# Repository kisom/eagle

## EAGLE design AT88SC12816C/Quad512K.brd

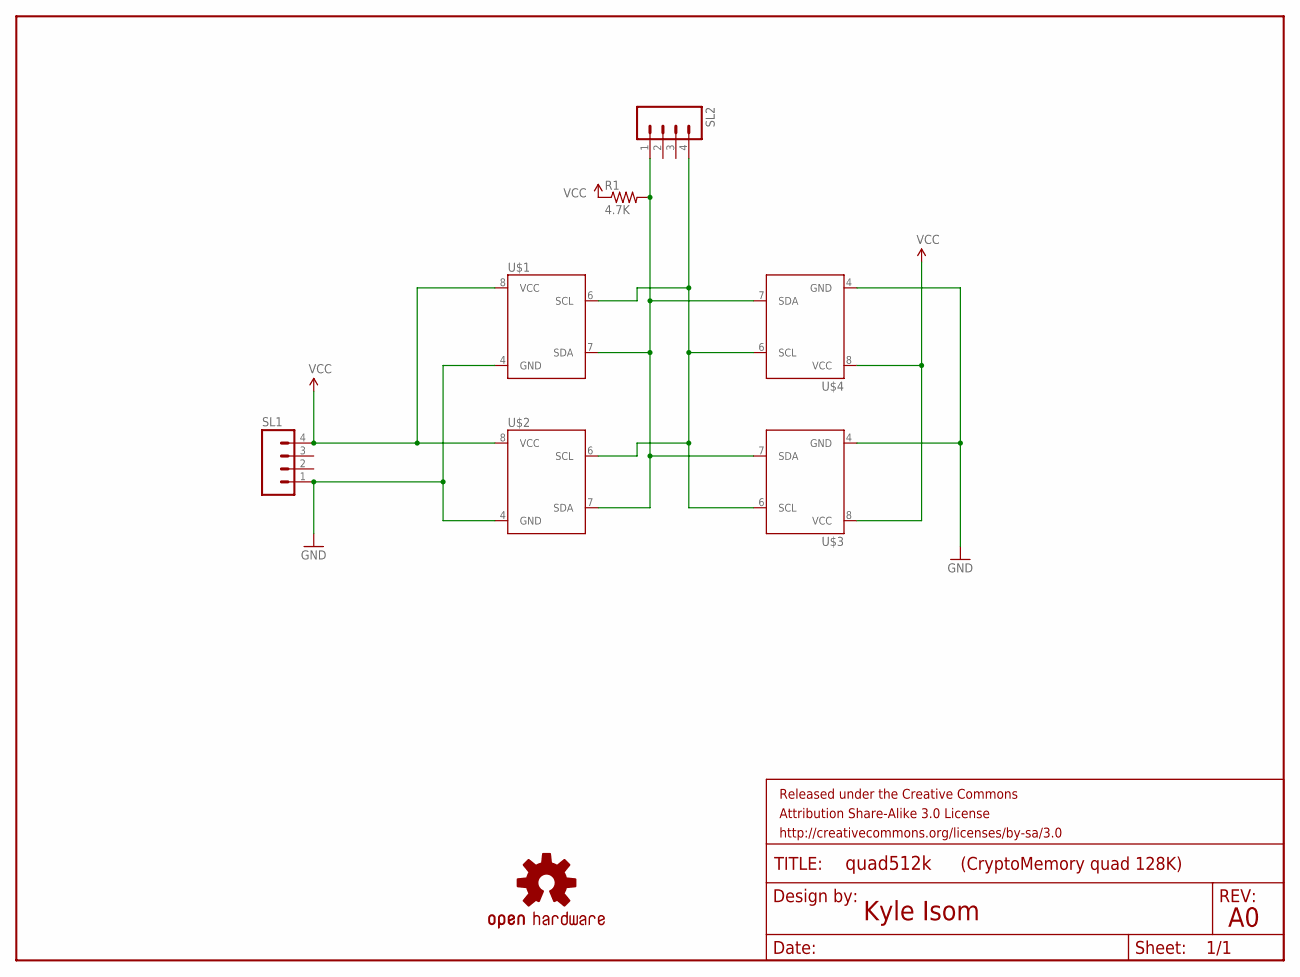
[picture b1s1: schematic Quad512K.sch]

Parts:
FRAME1: FRAME-LETTER; CREATIVE_COMMONS
LOGO1: OSHW-LOGOS; OSHW-LOGO-S
R1: 4.7K; AXIAL-0.4
SL1, SL2: M04LOCK; 1X04_LOCK
U$1, U$2, U$3, U$4: AT88SCAT88SC-PDIP; DIL08

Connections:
GND: SL1.1, U$1.4 (GND), U$2.4 (GND), U$3.4 (GND), U$4.4 (GND)
unnamed: SL2.4, U$1.6 (SCL), U$2.6 (SCL), U$3.6 (SCL), U$4.6 (SCL)
unnamed: R1.P$2 (2), SL2.1, U$1.7 (SDA), U$2.7 (SDA), U$3.7 (SDA), U$4.7 (SDA)
VCC: R1.P$1 (1), SL1.4, U$1.8 (VCC), U$2.8 (VCC), U$3.8 (VCC), U$4.8 (VCC)

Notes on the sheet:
(CryptoMemory quad 128K)
Kyle Isom

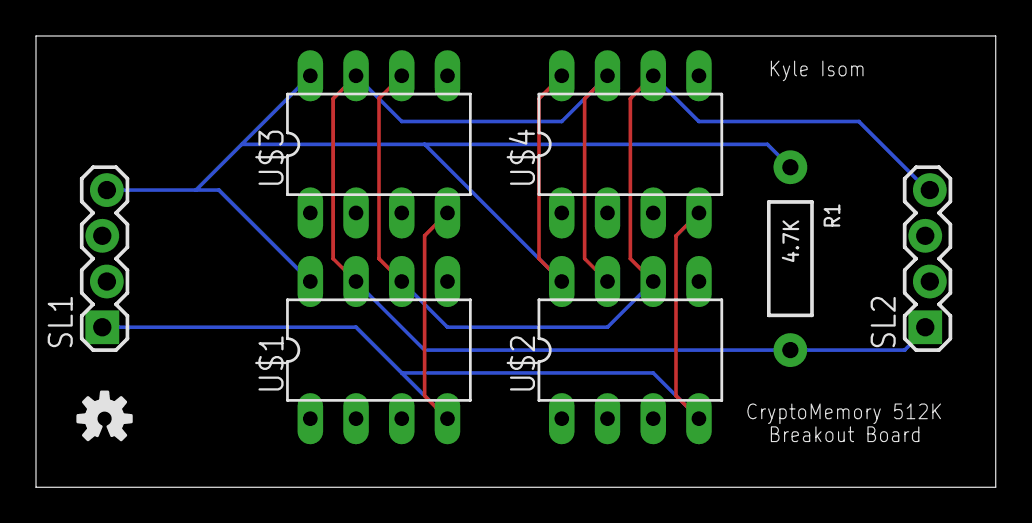
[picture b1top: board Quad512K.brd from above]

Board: 2 copper layers, 53.3 x 25.1 mm, 9 parts (0 on the bottom side), 4 nets.

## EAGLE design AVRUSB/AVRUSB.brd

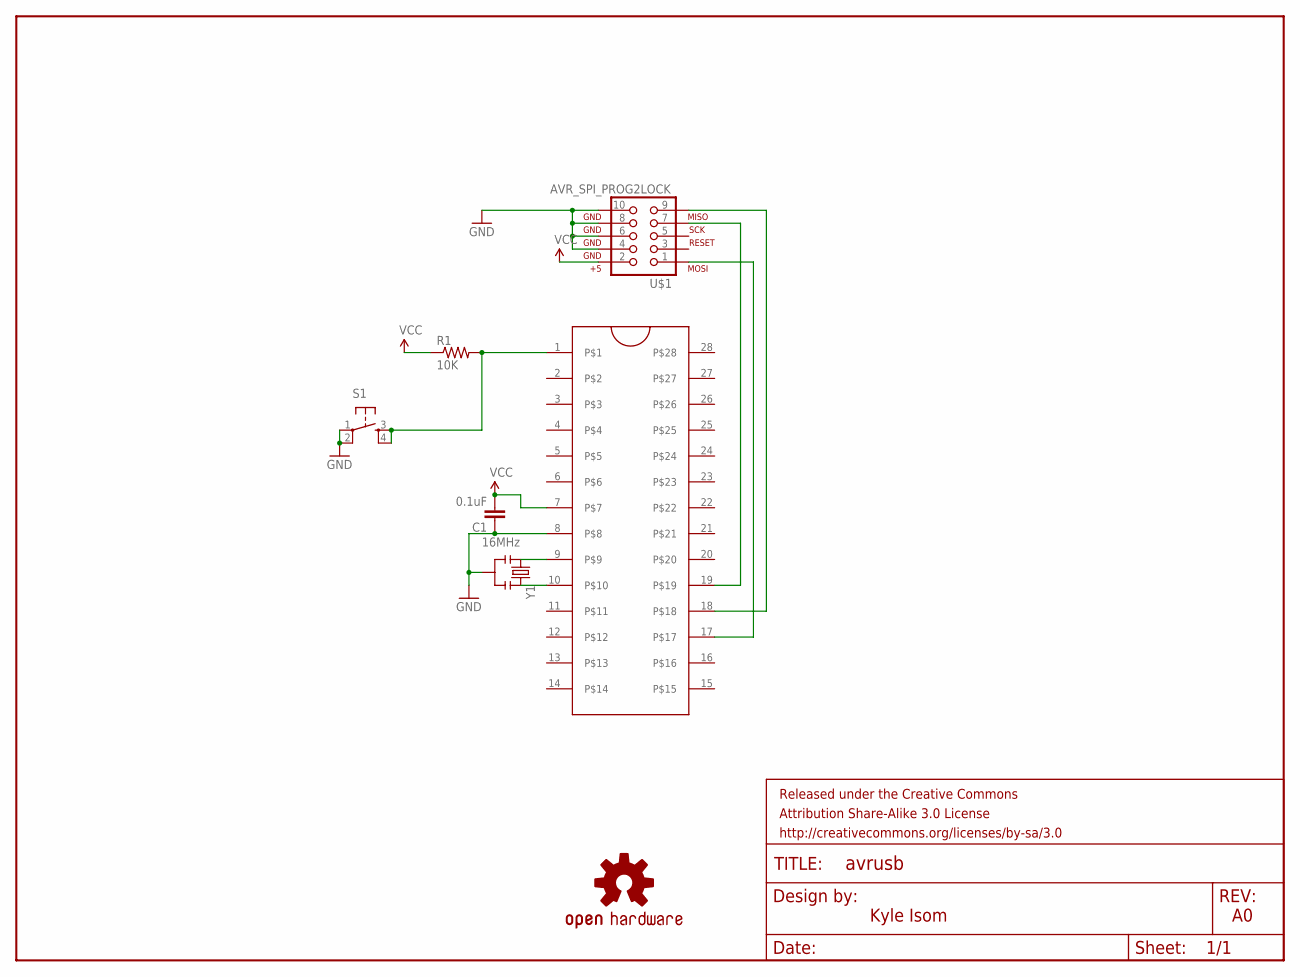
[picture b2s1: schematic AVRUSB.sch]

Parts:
C1: 0.1uF; CAP-PTH-SMALL
FRAME1: FRAME-LETTER; CREATIVE_COMMONS
LOGO1: OSHW-LOGOM; OSHW-LOGO-M
R1: 10K; AXIAL-0.4
S1: TAC_SWITCHPTH; TACTILE-PTH
U$1: AVR_SPI_PROG2LOCK; 2X5-SHROUDED_LOCK
U$2: ZIFSOCKET-28-3ZIFFSOCKET-28-3; DIL28-3-ZIF_SOCKET
Y1: 16MHz; RESONATOR-PTH

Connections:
GND: C1.1, S1.1, S1.2, U$1.4, U$1.6, U$1.8, U$1.10, U$2.8, Y1.2
unnamed: U$2.9, Y1.1
unnamed: U$2.10, Y1.3
unnamed: U$1.9, U$2.18
unnamed: U$1.1, U$2.17
unnamed: U$1.7, U$2.19
unnamed: R1.P$2 (2), S1.3, S1.4, U$2.1
VCC: C1.2, R1.P$1 (1), U$1.2, U$2.7

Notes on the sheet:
Kyle Isom

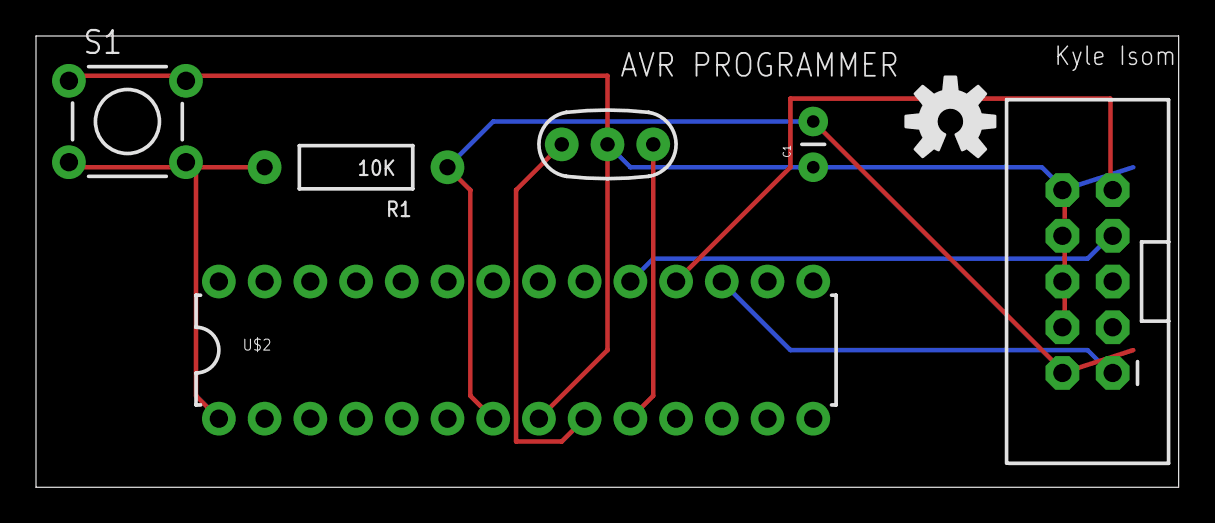
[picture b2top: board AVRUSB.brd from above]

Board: 2 copper layers, 63.5 x 25.1 mm, 9 parts (0 on the bottom side), 8 nets.

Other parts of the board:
U$3: OSHW-LOGO-M

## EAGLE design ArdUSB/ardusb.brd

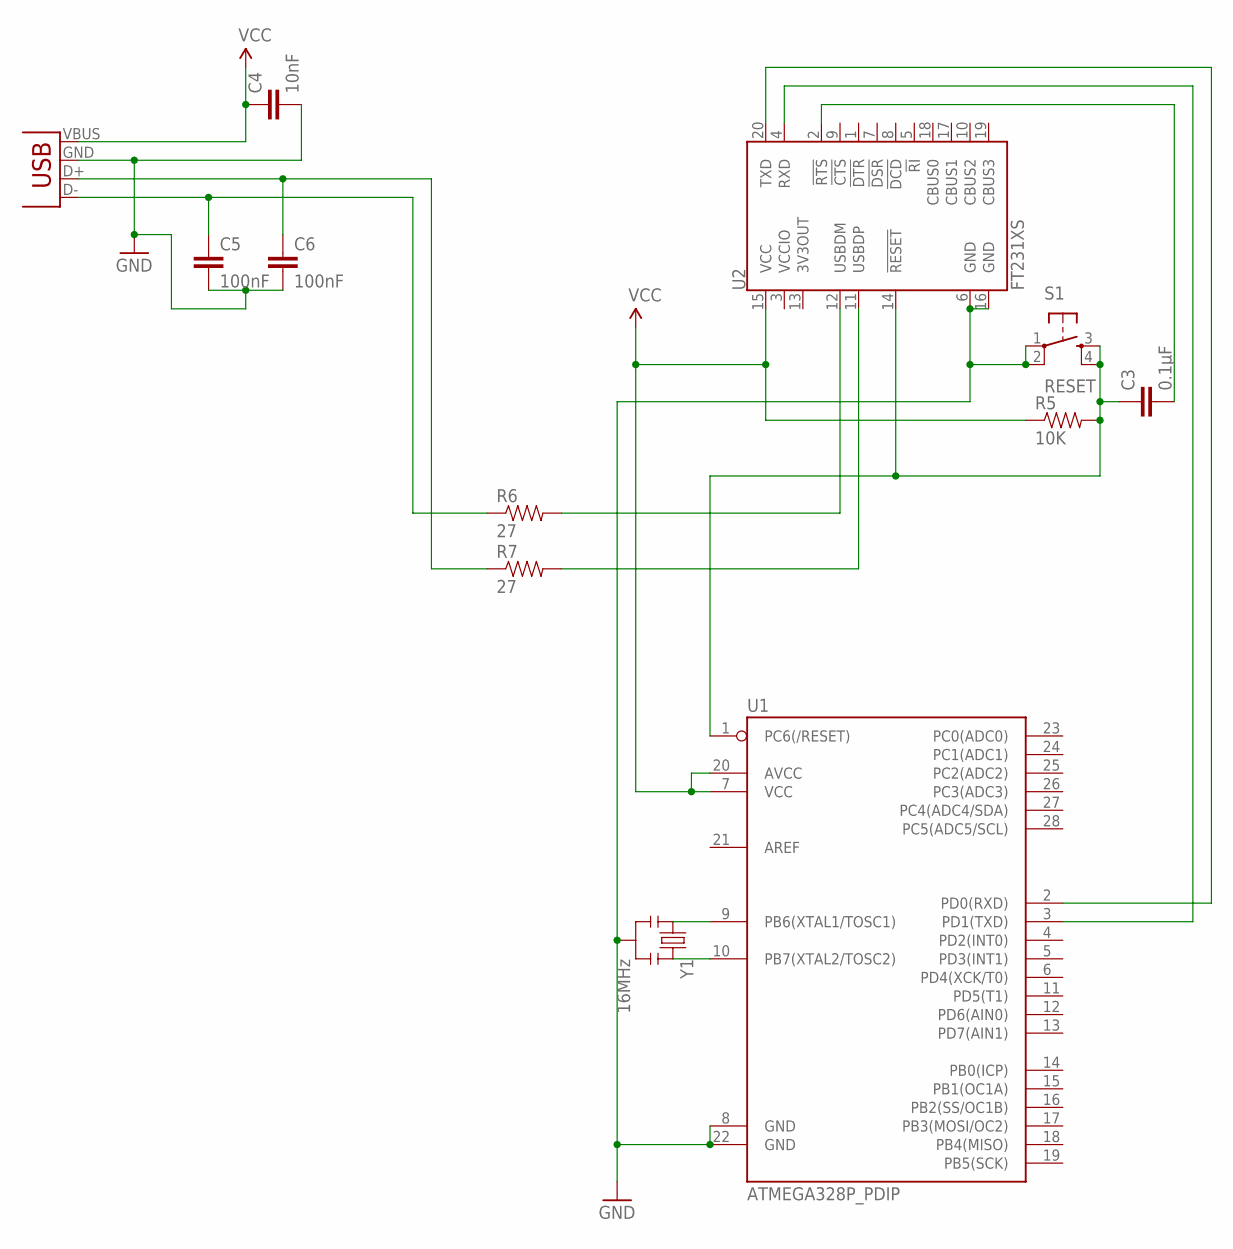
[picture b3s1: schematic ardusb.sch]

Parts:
C3: 0.1µF; CAP-PTH-SMALL
C4: 10nF; CAP-PTH-SMALL
C5, C6: 100nF; CAP-PTH-SMALL
JP1: USB-A-H
R5: 10K; AXIAL-0.6
R6, R7: 27; AXIAL-0.6
S1: RESET; TACTILE-PTH
U1: ATMEGA328P_PDIP; DIL28-3
U2: FT231XS; SSOP20_L
Y1: 16MHz; RESONATOR-PTH

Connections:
GND: C4.2, C5.2, C6.2, JP1.GND (VBUS), S1.1, S1.2, U1.8 (GND), U1.22 (GND), U2.6 (GND), U2.16 (GND), Y1.2
unnamed: U1.9 (PB6(XTAL1/TOSC1)), Y1.1
unnamed: U1.10 (PB7(XTAL2/TOSC2)), Y1.3
unnamed: C3.1, R5.P$2 (2), S1.3, S1.4, U1.1 (PC6(/RESET)), U2.14 (!RESET)
unnamed: C3.2, U2.2 (!RTS)
unnamed: R6.P$2 (2), U2.12 (USBDM)
unnamed: R7.P$2 (2), U2.11 (USBDP)
unnamed: U1.3 (PD1(TXD)), U2.4 (RXD)
unnamed: U1.2 (PD0(RXD)), U2.20 (TXD)
unnamed: C6.1, JP1.D+ (D-), R7.P$1 (1)
unnamed: C5.1, JP1.D- (D+), R6.P$1 (1)
VCC: C4.1, JP1.VBUS (GND), R5.P$1 (1), U1.7 (VCC), U1.20 (AVCC), U2.15 (VCC)

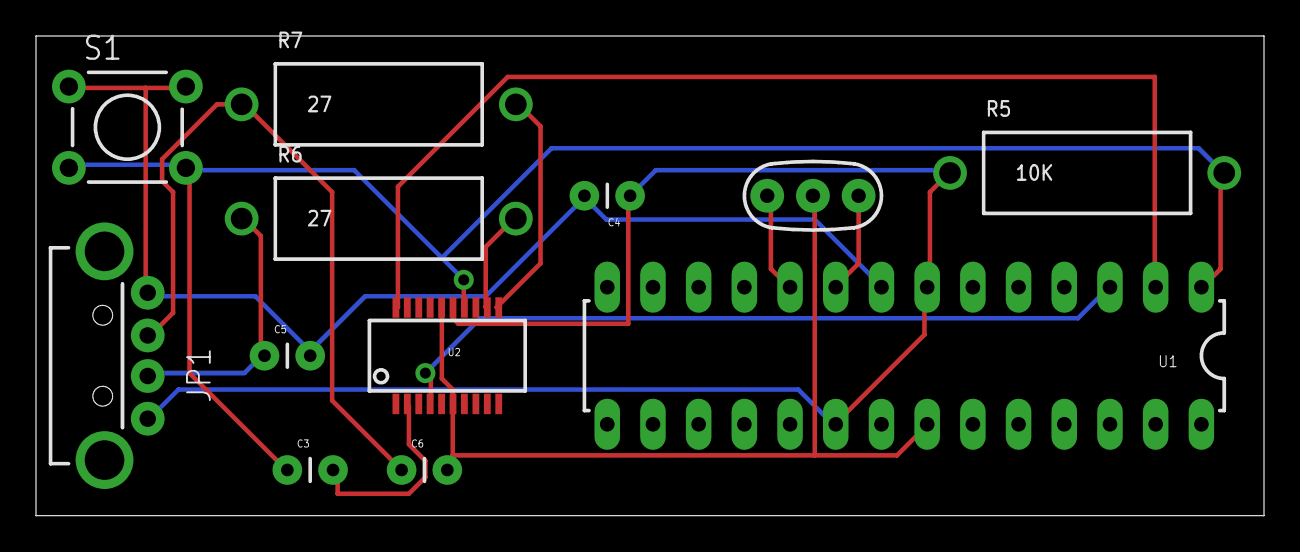
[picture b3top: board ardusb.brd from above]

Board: 2 copper layers, 68.2 x 26.7 mm, 12 parts (0 on the bottom side), 12 nets.

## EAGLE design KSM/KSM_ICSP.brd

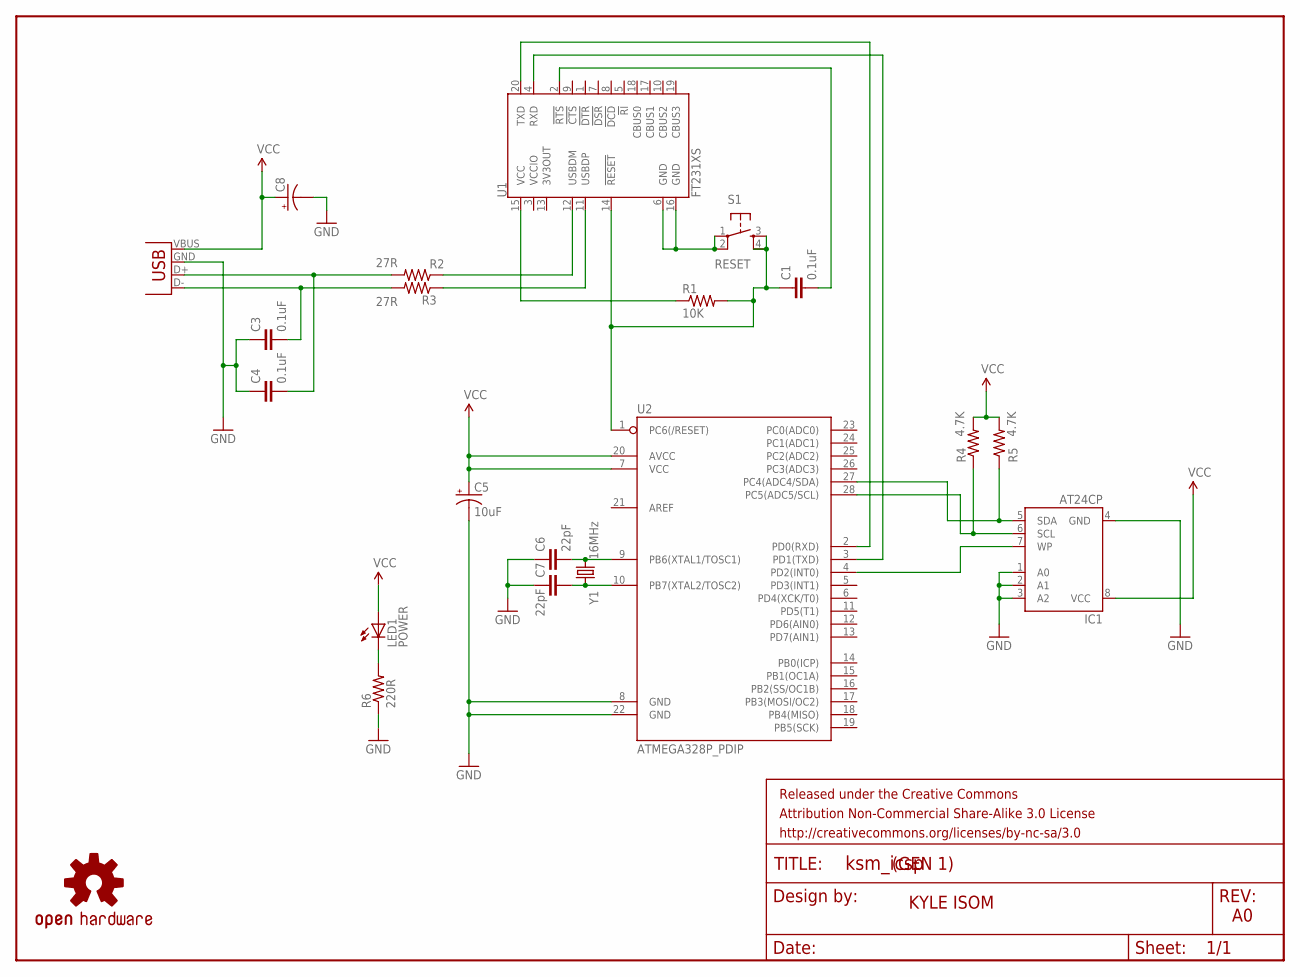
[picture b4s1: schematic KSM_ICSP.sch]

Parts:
C1, C3, C4: 0.1uF; CAP-PTH-SMALL
C5: 10uF; CPOL-RADIAL-10UF-25V
C6, C7: 22pF; CAP-PTH-SMALL
C8: CAP_POLPTH2; CPOL-RADIAL-10UF-25V
FRAME1: FRAME-LETTER; CREATIVE_COMMONS
IC1: AT24CP; DIL08
JP1: USB-A-H
LED1: POWER; LED3MM
LOGO1: OSHW-LOGOL; OSHW-LOGO-L
R1: 10K; AXIAL-0.4
R2, R3: 27R; AXIAL-0.4
R4, R5: 4.7K; AXIAL-0.4
R6: 220R; AXIAL-0.4
S1: RESET; TACTILE-PTH
U1: FT231XS; SSOP20_L
U2: ATMEGA328P_PDIP; DIL28-3
Y1: 16MHz; HC49US

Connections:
GND: C3.1, C4.1, C5.2 (-), C6.1, C7.1, C8.2 (-), IC1.1 (A0), IC1.2 (A1), IC1.3 (A2), IC1.4 (GND), JP1.GND (VBUS), R6.P$1 (1), U2.8 (GND), U2.22 (GND)
unnamed: C6.2, U2.9 (PB6(XTAL1/TOSC1)), Y1.2
unnamed: C7.2, U2.10 (PB7(XTAL2/TOSC2)), Y1.1
unnamed: IC1.7 (WP), U2.4 (PD2(INT0))
unnamed: IC1.6 (SCL), R4.P$1 (1), U2.28 (PC5(ADC5/SCL))
unnamed: IC1.5 (SDA), R5.P$1 (1), U2.27 (PC4(ADC4/SDA))
unnamed: R3.P$1 (1), U1.11 (USBDP)
unnamed: R2.P$1 (1), U1.12 (USBDM)
unnamed: C4.2, JP1.D+ (D-), R2.P$2 (2)
unnamed: C3.2, JP1.D- (D+), R3.P$2 (2)
unnamed: S1.1, S1.2, U1.6 (GND), U1.16 (GND)
unnamed: C1.1, R1.P$2 (2), S1.3, S1.4, U1.14 (!RESET), U2.1 (PC6(/RESET))
unnamed: C1.2, U1.2 (!RTS)
unnamed: R1.P$1 (1), U1.15 (VCC)
unnamed: LED1.K (C), R6.P$2 (2)
unnamed: U1.20 (TXD), U2.2 (PD0(RXD))
unnamed: U1.4 (RXD), U2.3 (PD1(TXD))
VCC: C5.1 (+), C8.1 (+), IC1.8 (VCC), JP1.VBUS (GND), LED1.A, R4.P$2 (2), R5.P$2 (2), U2.7 (VCC), U2.20 (AVCC)

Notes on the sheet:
KYLE ISOM
(GEN 1)

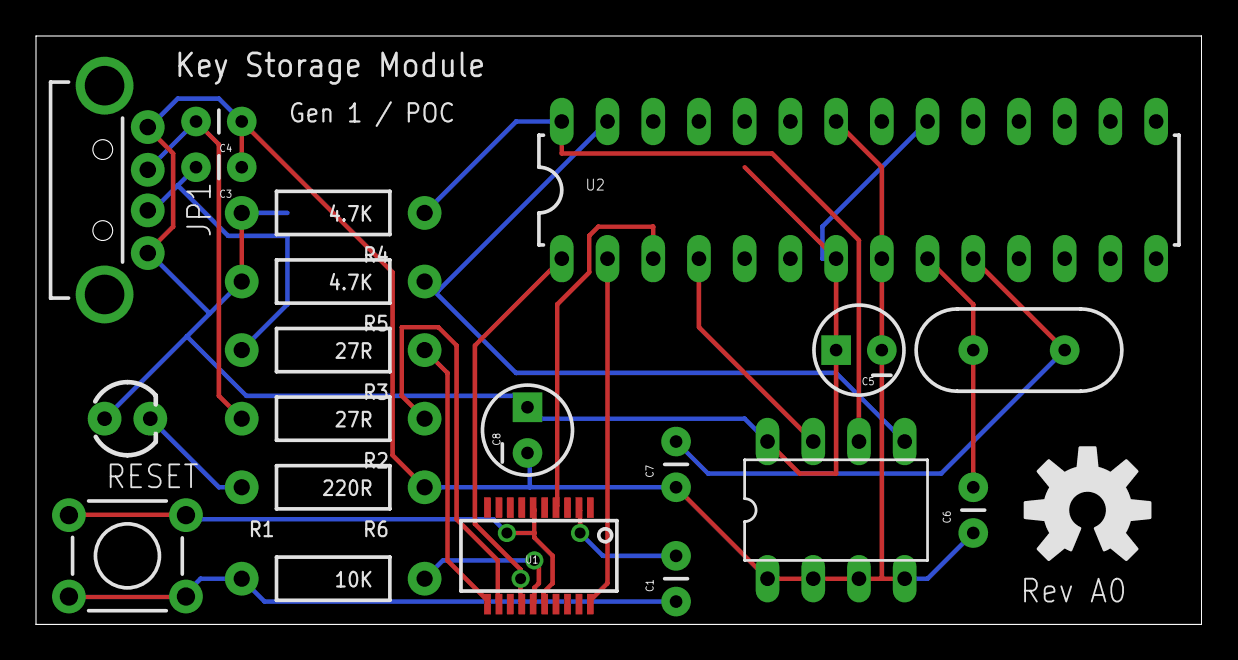
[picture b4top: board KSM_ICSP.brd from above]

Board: 2 copper layers, 64.8 x 32.7 mm, 22 parts (0 on the bottom side), 18 nets.

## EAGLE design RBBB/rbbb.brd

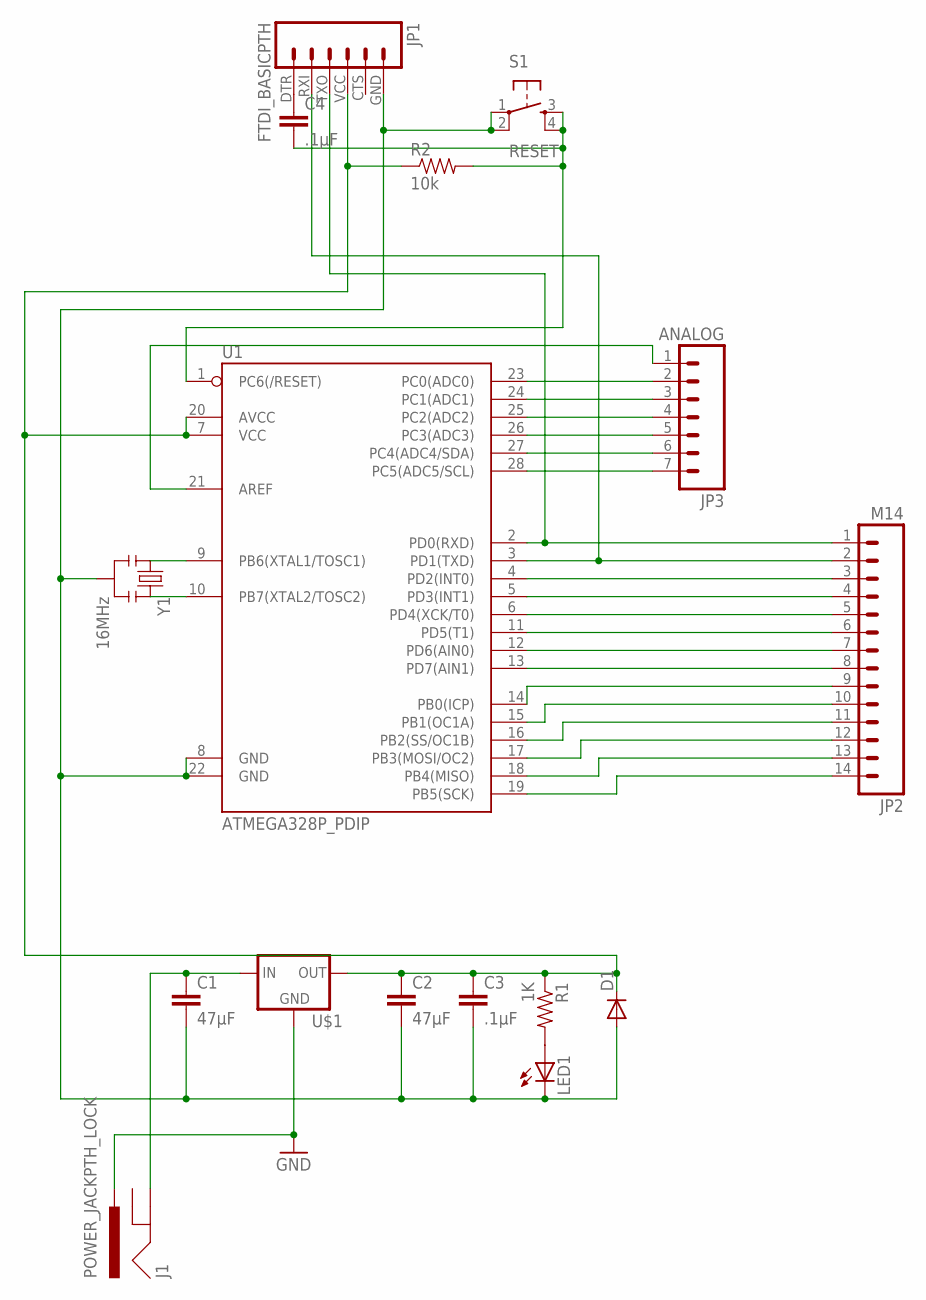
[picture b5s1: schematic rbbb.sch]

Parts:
C1, C2: 47µF; CAP-PTH-SMALL
C3, C4: .1µF; CAP-PTH-SMALL
D1: DIODEPTH; DIODE-1N4001
J1: POWER_JACKPTH_LOCK; POWER_JACK_PTH_LOCK
JP1: FTDI_BASICPTH; FTDI_BASIC
JP2: M14; 1X14
JP3: ANALOG; 1X07
LED1: LED5MM
R1: 1K; AXIAL-0.4
R2: 10k; AXIAL-0.4
S1: RESET; TACTILE-PTH
U1: ATMEGA328P_PDIP; DIL28-3
U$1: V_REG_78XX-TO-220; TO-220-ALT
Y1: 16MHz; RESONATOR-PTH

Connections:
GND: J1.PWR, U$1.GND
unnamed: U1.9 (PB6(XTAL1/TOSC1)), Y1.1
unnamed: U1.10 (PB7(XTAL2/TOSC2)), Y1.3
unnamed: LED1.A, R1.P$2 (2)
unnamed: C2.1, C3.1, D1.C, JP1.VCC (4), R1.P$1 (1), R2.P$1 (1), U1.7 (VCC), U1.20 (AVCC), U$1.OUT
unnamed: C1.2, C2.2, C3.2, D1.A, JP1.GND (6), LED1.K (C), S1.1, S1.2, U1.8 (GND), U1.22 (GND), Y1.2
unnamed: JP1.TXO (3), JP2.1, U1.2 (PD0(RXD))
unnamed: C1.1, J1.GND, U$1.IN
unnamed: JP1.RXI (2), JP2.2, U1.3 (PD1(TXD))
unnamed: JP2.3, U1.4 (PD2(INT0))
unnamed: C4.2, R2.P$2 (2), S1.3, S1.4, U1.1 (PC6(/RESET))
unnamed: JP2.4, U1.5 (PD3(INT1))
unnamed: JP2.5, U1.6 (PD4(XCK/T0))
unnamed: C4.1, JP1.DTR (1)
unnamed: JP2.6, U1.11 (PD5(T1))
unnamed: JP2.7, U1.12 (PD6(AIN0))
unnamed: JP2.8, U1.13 (PD7(AIN1))
unnamed: JP2.9, U1.14 (PB0(ICP))
unnamed: JP2.10, U1.15 (PB1(OC1A))
unnamed: JP2.11, U1.16 (PB2(SS/OC1B))
unnamed: JP2.12, U1.17 (PB3(MOSI/OC2))
unnamed: JP2.13, U1.18 (PB4(MISO))
unnamed: JP2.14, U1.19 (PB5(SCK))
unnamed: JP3.1, U1.21 (AREF)
unnamed: JP3.2, U1.23 (PC0(ADC0))
unnamed: JP3.3, U1.24 (PC1(ADC1))
unnamed: JP3.4, U1.25 (PC2(ADC2))
unnamed: JP3.5, U1.26 (PC3(ADC3))
unnamed: JP3.6, U1.27 (PC4(ADC4/SDA))
unnamed: JP3.7, U1.28 (PC5(ADC5/SCL))

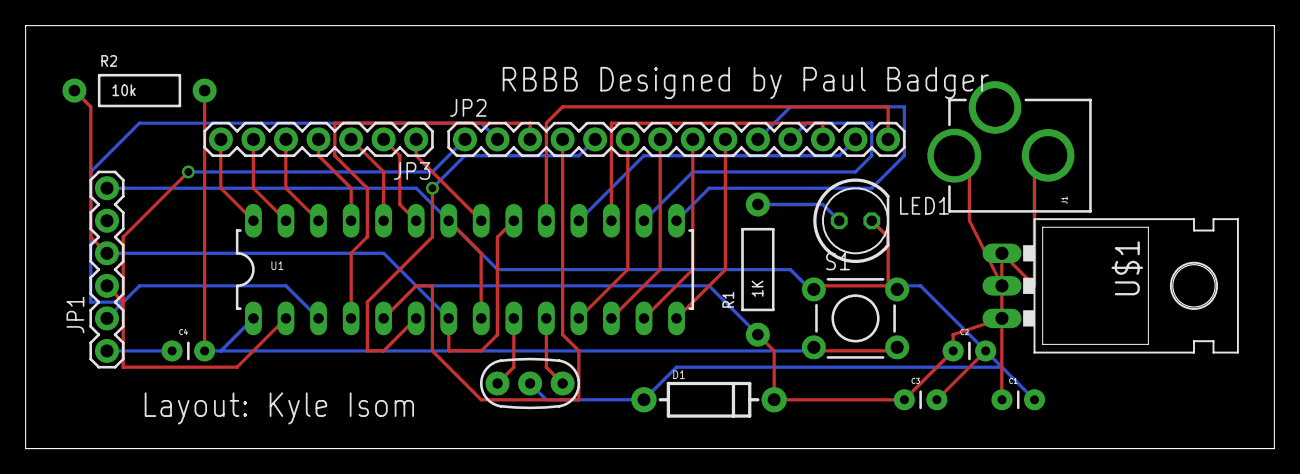
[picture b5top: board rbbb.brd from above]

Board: 2 copper layers, 97.5 x 33.0 mm, 16 parts (0 on the bottom side), 30 nets.

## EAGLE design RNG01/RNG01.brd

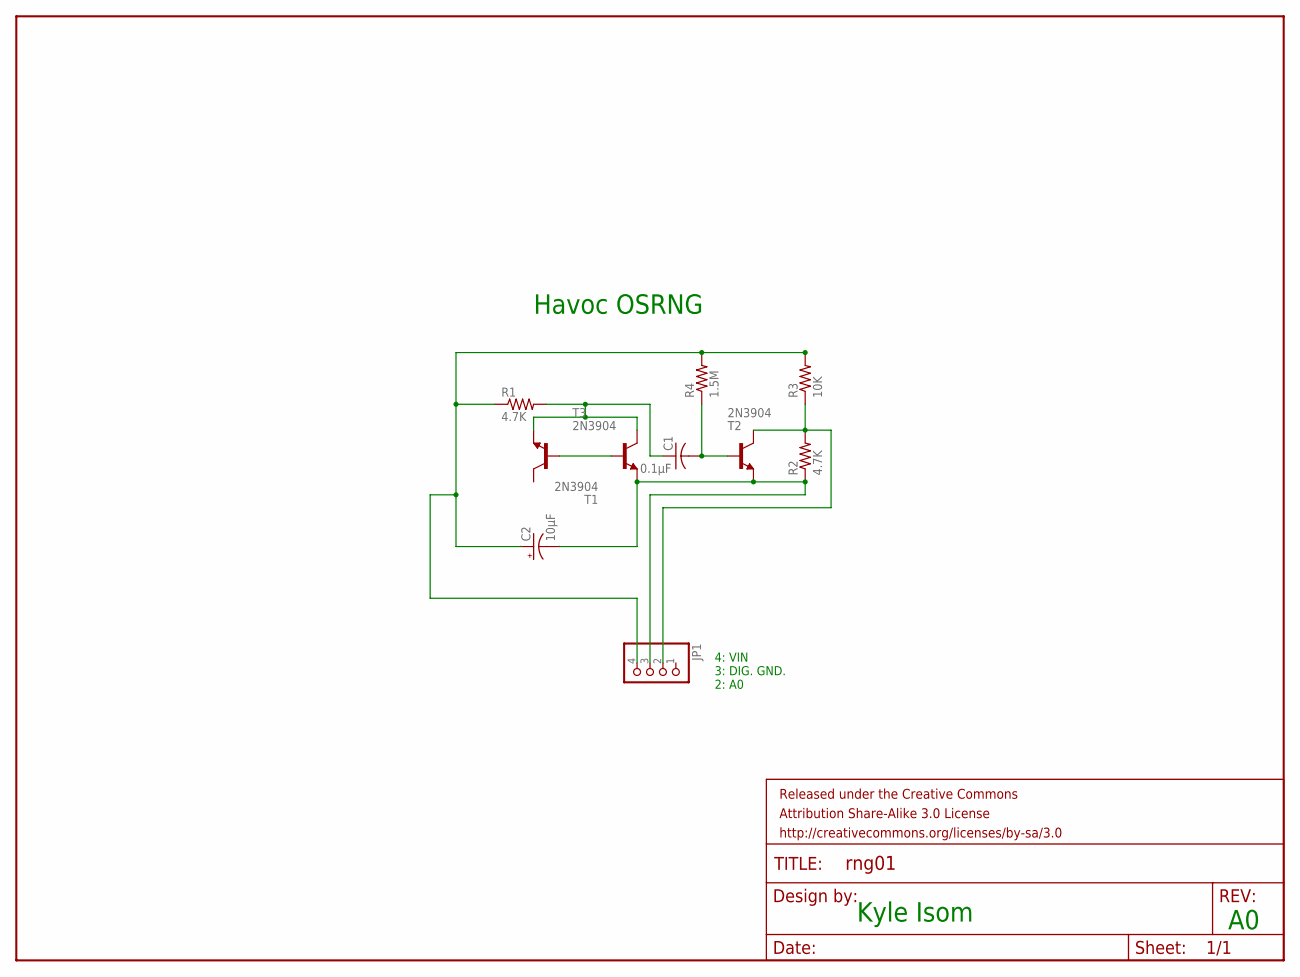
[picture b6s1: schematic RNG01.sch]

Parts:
C1: 0.1µF; C050-030X075
C2: 10µF; E2-5
FRAME1: FRAME-LETTER; CREATIVE_COMMONS
JP1: PINHD-1X4; 1X04
R1, R2: 4.7K; 0207/7
R3: 10K; 0207/7
R4: 1.5M; 0207/7
T1, T2, T3: 2N3904; TO92

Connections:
unnamed: T1.2 (B), T3.2 (B)
unnamed: C1.1, R1.2, T1.3 (E), T3.1 (C)
unnamed: JP1.2, R2.2, R3.1, T2.1 (C)
unnamed: C2.-, JP1.3, R2.1, T2.3 (E), T3.3 (E)
unnamed: C2.+, JP1.4, R1.1, R3.2, R4.2
unnamed: C1.2, R4.1, T2.2 (B)

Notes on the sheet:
4: VIN 3: DIG. GND. 2: A0
Kyle Isom
Havoc OSRNG

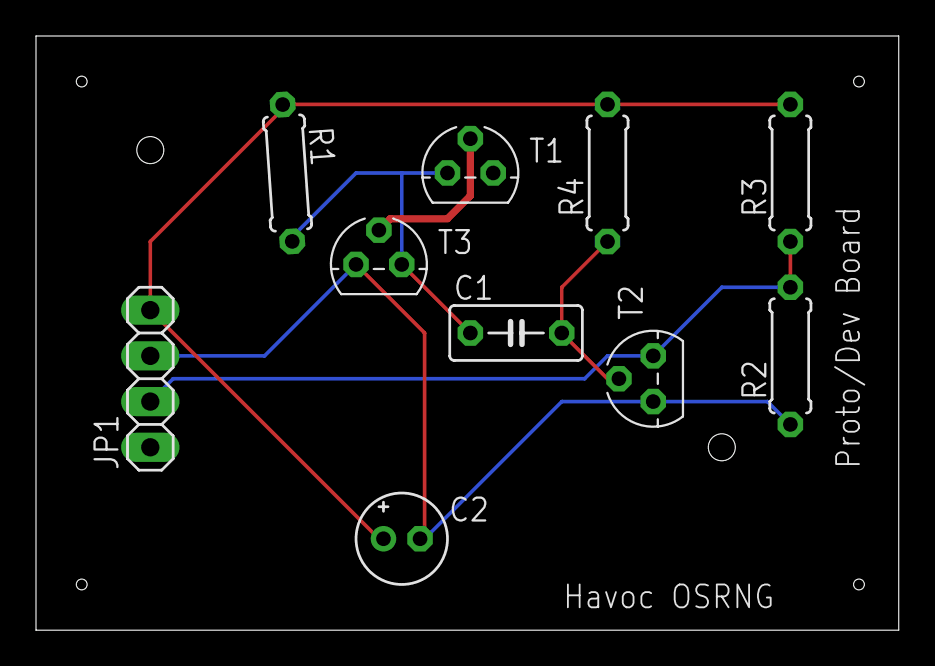
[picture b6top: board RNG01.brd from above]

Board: 2 copper layers, 47.9 x 33.0 mm, 11 parts (0 on the bottom side), 6 nets.

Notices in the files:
parts and their libraries:
SparkFun-Aesthetics: Licensing: CC v3.0 Share-Alike You are welcome to use this library for commercial purposes.
SparkFun-Aesthetics: Released under the Creative Commons Attribution Share-Alike 3.0 License
SparkFun-Aesthetics: http://creativecommons.org/licenses/by-sa/3.0
